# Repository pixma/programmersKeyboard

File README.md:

programmersKeyboard
===================
- Final Sem project

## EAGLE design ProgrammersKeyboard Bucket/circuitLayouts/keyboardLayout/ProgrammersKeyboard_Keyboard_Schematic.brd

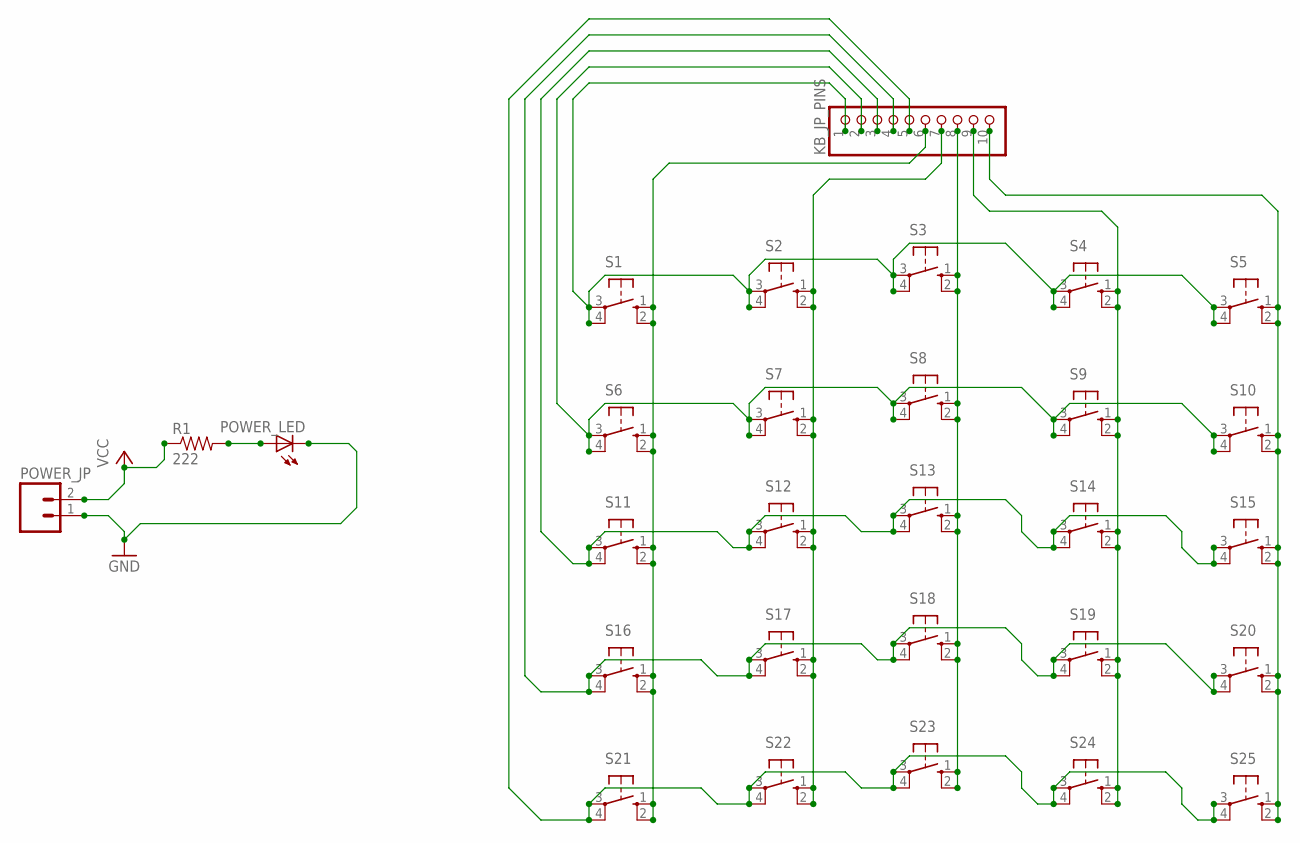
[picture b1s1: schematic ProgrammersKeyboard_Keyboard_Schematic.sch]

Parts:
KB_JP_PINS: PINHD-1X10/90; 1X10/90
POWER_JP: M02PTH3; 1X02_LONGPADS
POWER_LED: LEDSMT1206; 1206
R1: 222; 1206
S1, S2, S3, S4, S5, S6, S7, S8, S9, S10, S11, S12, S13, S14, S15, S16, S17, S18, S19, S20, S21, S22, S23, S24, S25: 10-XX; B3F-10XX

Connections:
GND: POWER_JP.1, POWER_LED.C
unnamed: KB_JP_PINS.3, S11.3, S11.4 (P1), S12.3, S12.4 (P1), S13.3, S13.4 (P1), S14.3, S14.4 (P1), S15.3, S15.4 (P1)
unnamed: KB_JP_PINS.4, S16.3, S16.4 (P1), S17.3, S17.4 (P1), S18.3, S18.4 (P1), S19.3, S19.4 (P1), S20.3, S20.4 (P1)
unnamed: KB_JP_PINS.5, S21.3, S21.4 (P1), S22.3, S22.4 (P1), S23.3, S23.4 (P1), S24.3, S24.4 (P1), S25.3, S25.4 (P1)
unnamed: POWER_LED.A, R1.2
unnamed: KB_JP_PINS.10, S5.1 (S), S5.2 (S1), S10.1 (S), S10.2 (S1), S15.1 (S), S15.2 (S1), S20.1 (S), S20.2 (S1), S25.1 (S), S25.2 (S1)
unnamed: KB_JP_PINS.6, S1.1 (S), S1.2 (S1), S6.1 (S), S6.2 (S1), S11.1 (S), S11.2 (S1), S16.1 (S), S16.2 (S1), S21.1 (S), S21.2 (S1)
unnamed: KB_JP_PINS.1, S1.3, S1.4 (P1), S2.3, S2.4 (P1), S3.3, S3.4 (P1), S4.3, S4.4 (P1), S5.3, S5.4 (P1)
unnamed: KB_JP_PINS.7, S2.1 (S), S2.2 (S1), S7.1 (S), S7.2 (S1), S12.1 (S), S12.2 (S1), S17.1 (S), S17.2 (S1), S22.1 (S), S22.2 (S1)
unnamed: KB_JP_PINS.8, S3.1 (S), S3.2 (S1), S8.1 (S), S8.2 (S1), S13.1 (S), S13.2 (S1), S18.1 (S), S18.2 (S1), S23.1 (S), S23.2 (S1)
unnamed: KB_JP_PINS.9, S4.1 (S), S4.2 (S1), S9.1 (S), S9.2 (S1), S14.1 (S), S14.2 (S1), S19.1 (S), S19.2 (S1), S24.1 (S), S24.2 (S1)
unnamed: KB_JP_PINS.2, S6.3, S6.4 (P1), S7.3, S7.4 (P1), S8.3, S8.4 (P1), S9.3, S9.4 (P1), S10.3, S10.4 (P1)
VCC: POWER_JP.2, R1.1

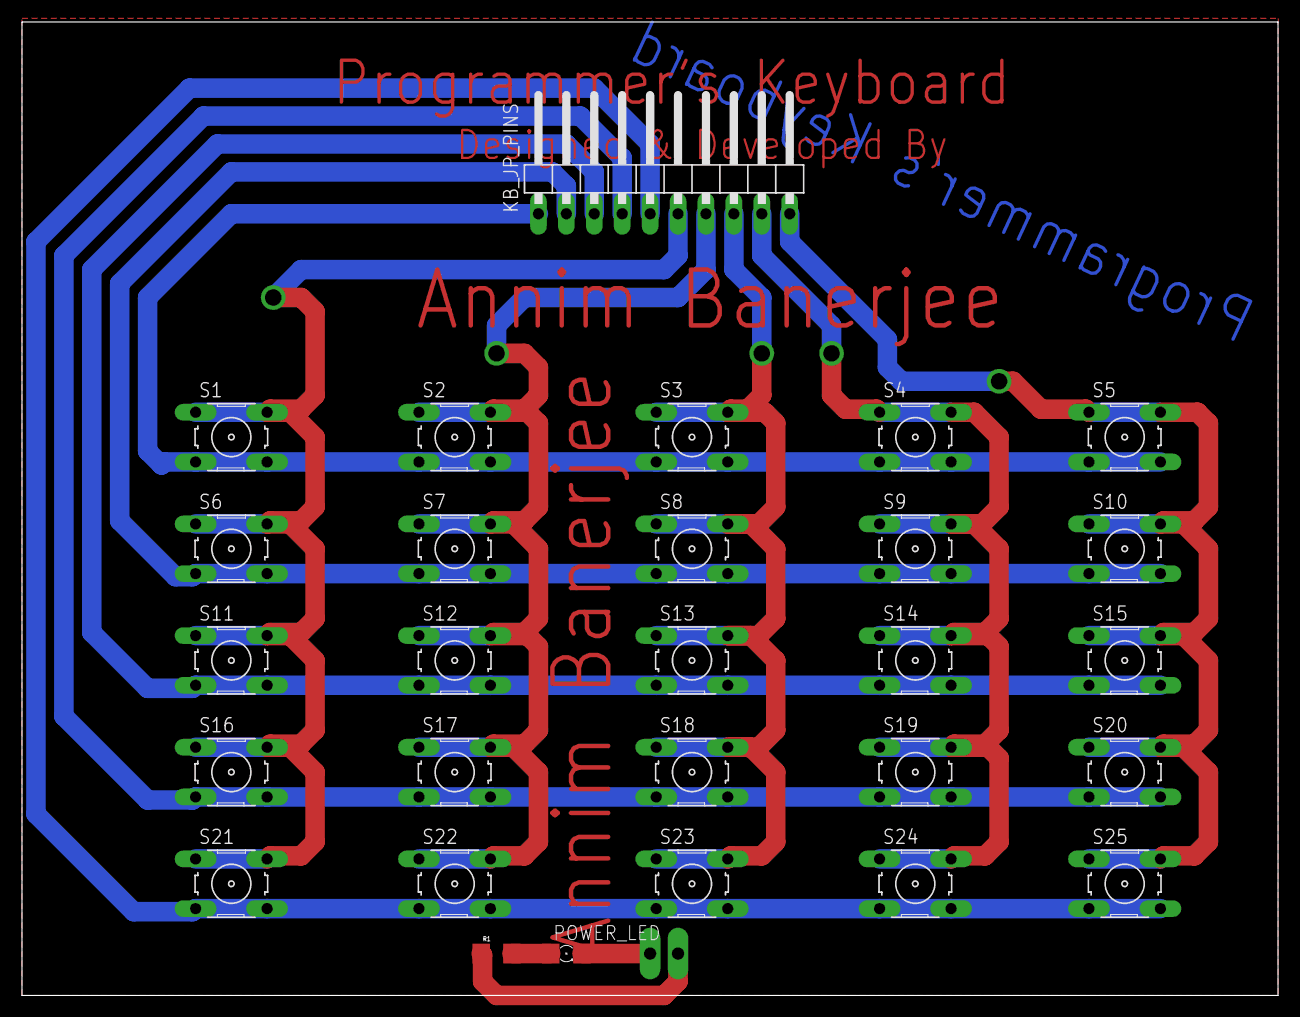
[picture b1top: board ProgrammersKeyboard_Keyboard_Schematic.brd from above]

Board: 2 copper layers, 114.3 x 88.6 mm, 29 parts (0 on the bottom side), 13 nets.

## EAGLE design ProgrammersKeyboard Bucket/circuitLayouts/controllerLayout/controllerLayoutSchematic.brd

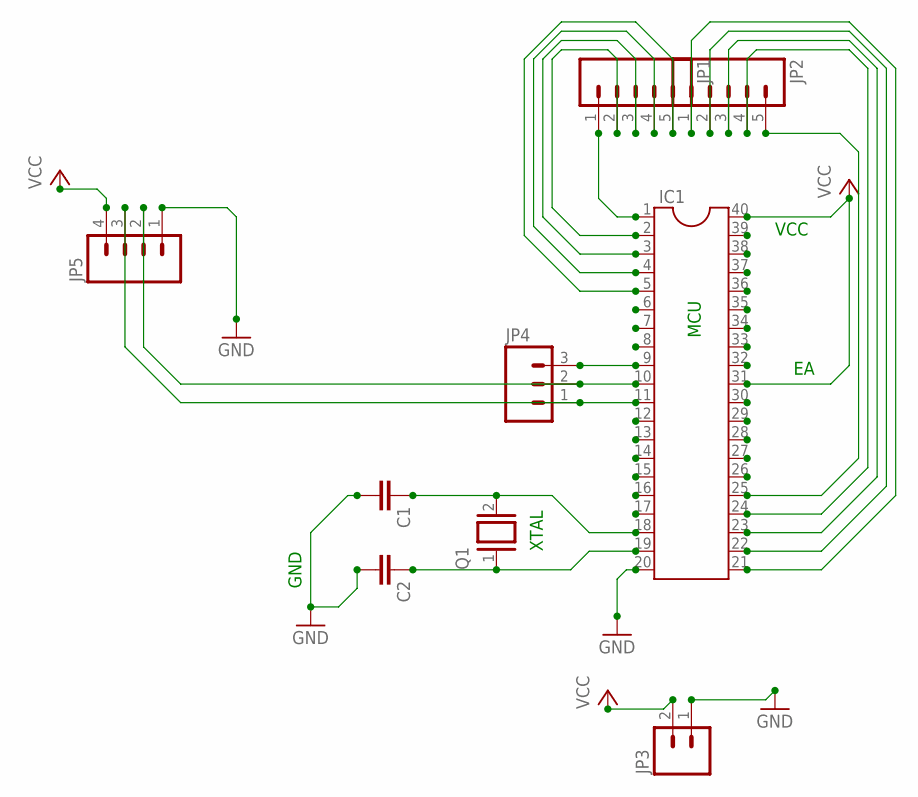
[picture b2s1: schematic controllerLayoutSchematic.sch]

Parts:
C1, C2: CAPPTH2; CAP-PTH-SMALL2
IC1: DIL40
JP1, JP2: M05PTH_LONGPADS; 1X05_LONGPADS
JP3: M02PTH3; 1X02_LONGPADS
JP4: M03LONGPADS; 1X03_LONGPADS
JP5: M04SMD; 1X04-SMD
Q1: XTAL; Q

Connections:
GND: C1.2, C2.2, IC1.20, JP3.1, JP5.1
unnamed: IC1.1, JP1.1
unnamed: IC1.9, JP4.3
unnamed: IC1.10, JP4.2, JP5.2
unnamed: IC1.11, JP4.1, JP5.3
unnamed: C1.1, IC1.18, Q1.2
unnamed: IC1.21, JP2.1
unnamed: IC1.23, JP2.3
unnamed: IC1.25, JP2.5
unnamed: IC1.24, JP2.4
unnamed: IC1.22, JP2.2
unnamed: IC1.5, JP1.5
unnamed: IC1.4, JP1.4
unnamed: IC1.3, JP1.3
unnamed: IC1.2, JP1.2
unnamed: C2.1, IC1.19, Q1.1
VCC: IC1.31, IC1.40, JP3.2, JP5.4

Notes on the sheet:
VCC
GND
XTAL
MCU

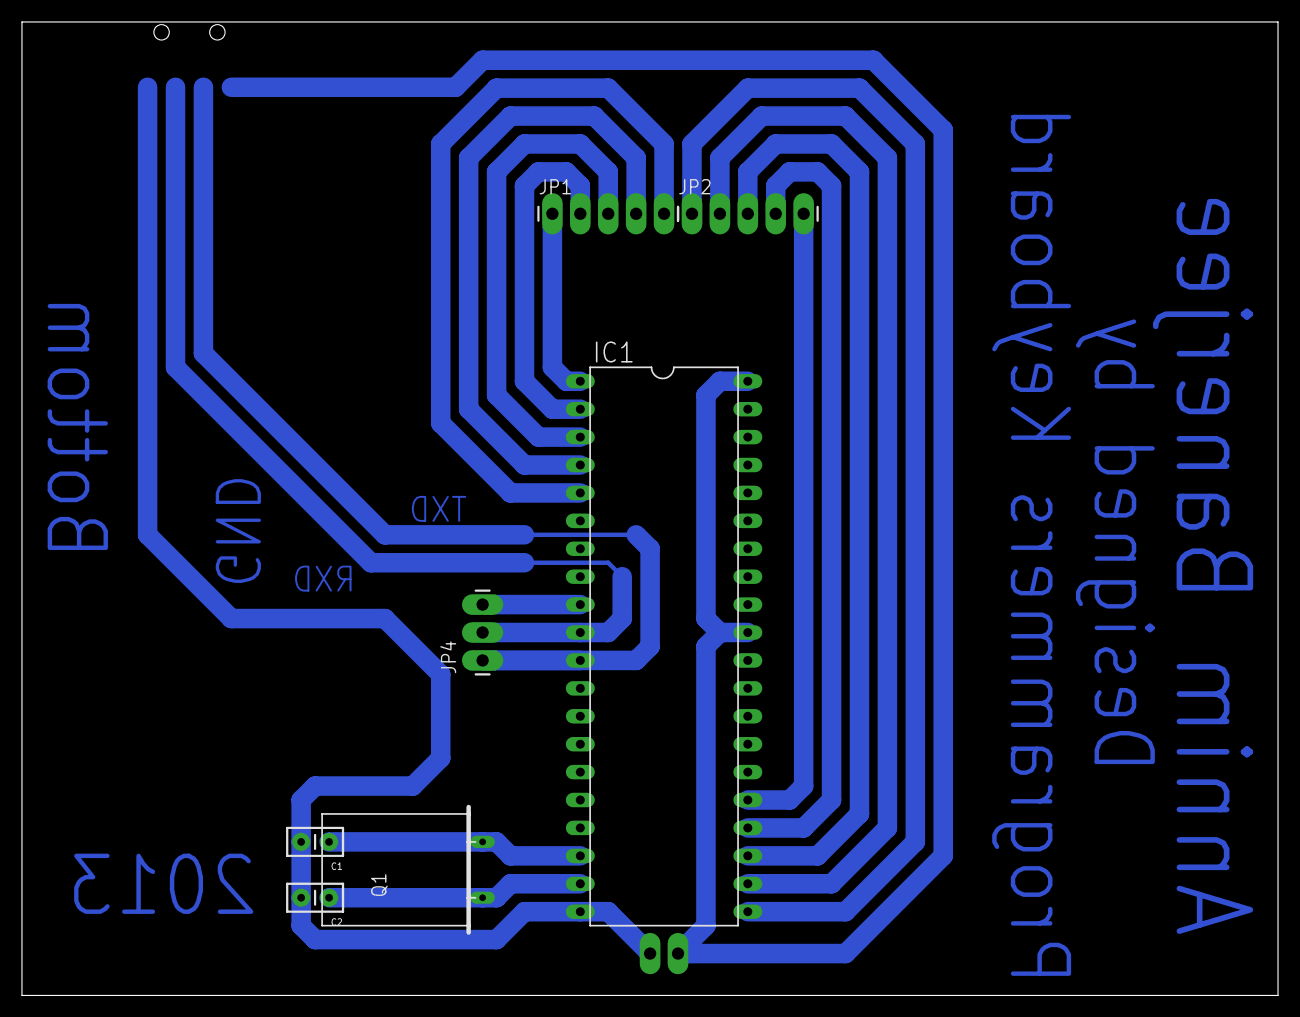
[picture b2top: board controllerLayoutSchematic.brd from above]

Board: 2 copper layers, 114.3 x 88.6 mm, 9 parts (1 on the bottom side), 17 nets.

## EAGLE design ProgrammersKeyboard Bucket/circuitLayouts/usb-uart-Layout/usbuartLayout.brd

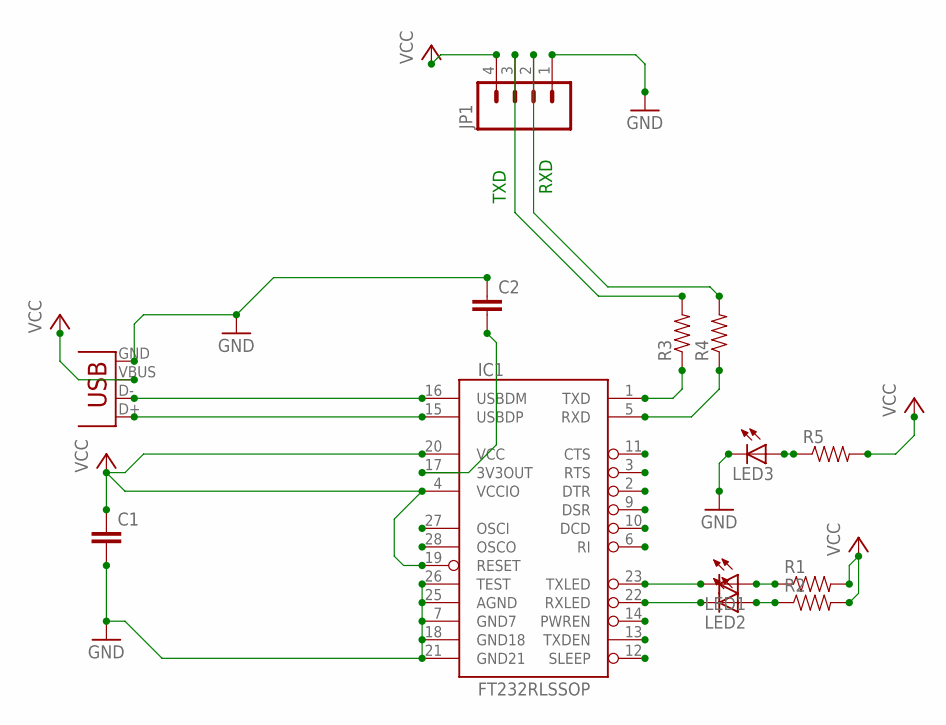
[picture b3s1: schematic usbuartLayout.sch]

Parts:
C1, C2: CAP1206; 1206
IC1: FT232RLSSOP; SSOP28DB
JP1: M04SMD; 1X04-SMD
LED1, LED2, LED3: LEDCHIPLED_1206; CHIPLED_1206
R1, R2, R3, R4, R5: RESISTOR1206; 1206
X1: USB-SMD-NS; USB-MINIB-NOSTOP

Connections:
GND: C1.2, C2.1, IC1.7 (GND7), IC1.18 (GND18), IC1.21 (GND21), IC1.25 (AGND), IC1.26 (TEST), JP1.1, LED3.C, X1.GND
unnamed: IC1.1 (TXD), R3.1
unnamed: JP1.3, R3.2
unnamed: IC1.15 (USBDP), X1.D+
unnamed: IC1.16 (USBDM), X1.D-
unnamed: LED3.A, R5.1
unnamed: C2.2, IC1.17 (3V3OUT)
unnamed: IC1.5 (RXD), R4.1
unnamed: JP1.2, R4.2
unnamed: IC1.22 (RXLED), LED2.C
unnamed: IC1.23 (TXLED), LED1.C
unnamed: LED2.A, R2.1
unnamed: LED1.A, R1.1
VCC: C1.1, IC1.4 (VCCIO), IC1.19 (RESET), IC1.20 (VCC), JP1.4, R1.2, R2.2, R5.2, X1.VBUS

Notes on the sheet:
TXD
RXD

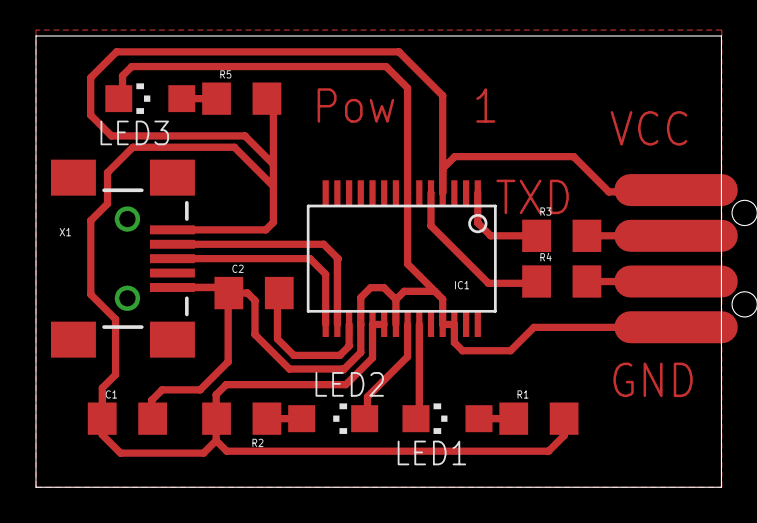
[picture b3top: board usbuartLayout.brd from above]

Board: 2 copper layers, 38.1 x 25.1 mm, 13 parts (0 on the bottom side), 14 nets.

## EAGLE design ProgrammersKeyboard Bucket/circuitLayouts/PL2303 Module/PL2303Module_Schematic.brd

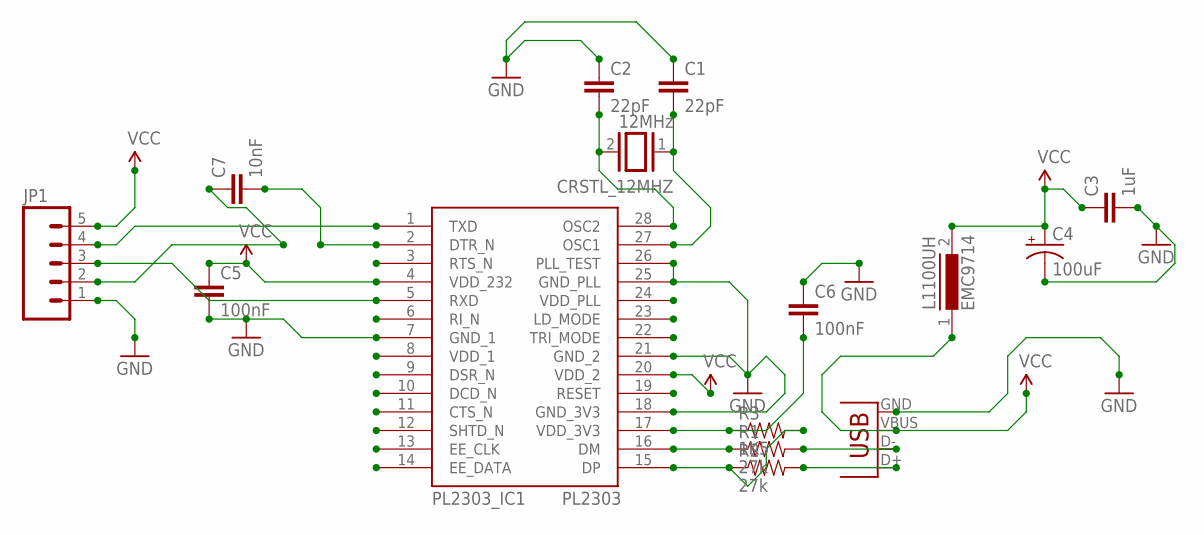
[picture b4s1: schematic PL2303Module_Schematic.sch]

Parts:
C1, C2: 22pF; 1206
C3: 1uF; CAP-PTH-SMALL2
C4: 100uF; CPOL-RADIAL-100UF-25V
C5: 100nF; CAP-PTH-SMALL2
C6: 100nF; 1206
C7: 10nF; 1206
CRSTL_12MHZ: 12MHz; Q
JP1: M05PTH_LONGPADS; 1X05_LONGPADS
L1100UH: EMC9714
PL2303_IC1: PL2303-SSOP28
R1, R2: 27k; 0805
R3: 1K5; 1206
X1: USBSMD; USB-MINIB

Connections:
GND: C1.1, C2.1, C3.2, C4.2 (-), C5.2, C6.1, JP1.1, PL2303_IC1.7 (GND_1), PL2303_IC1.18 (GND_3V3), PL2303_IC1.21 (GND_2), PL2303_IC1.25 (GND_PLL), PL2303_IC1.26 (PLL_TEST), X1.GND
unnamed: C7.1, JP1.2
unnamed: R1.2, X1.D-
unnamed: C7.2, PL2303_IC1.2 (DTR_N)
unnamed: C2.2, CRSTL_12MHZ.2, PL2303_IC1.28 (OSC2)
unnamed: C1.2, CRSTL_12MHZ.1, PL2303_IC1.27 (OSC1)
unnamed: PL2303_IC1.16 (DM), R1.1
unnamed: R2.2, X1.D+
unnamed: C6.2, PL2303_IC1.17 (VDD_3V3), R3.1
unnamed: JP1.3, PL2303_IC1.5 (RXD)
unnamed: PL2303_IC1.15 (DP), R2.1, R3.2
unnamed: JP1.4, PL2303_IC1.1 (TXD)
VCC: C3.1, C4.1 (+), C5.1, JP1.5, L1100UH.1, L1100UH.2, PL2303_IC1.4 (VDD_232), PL2303_IC1.20 (VDD_2), X1.VBUS

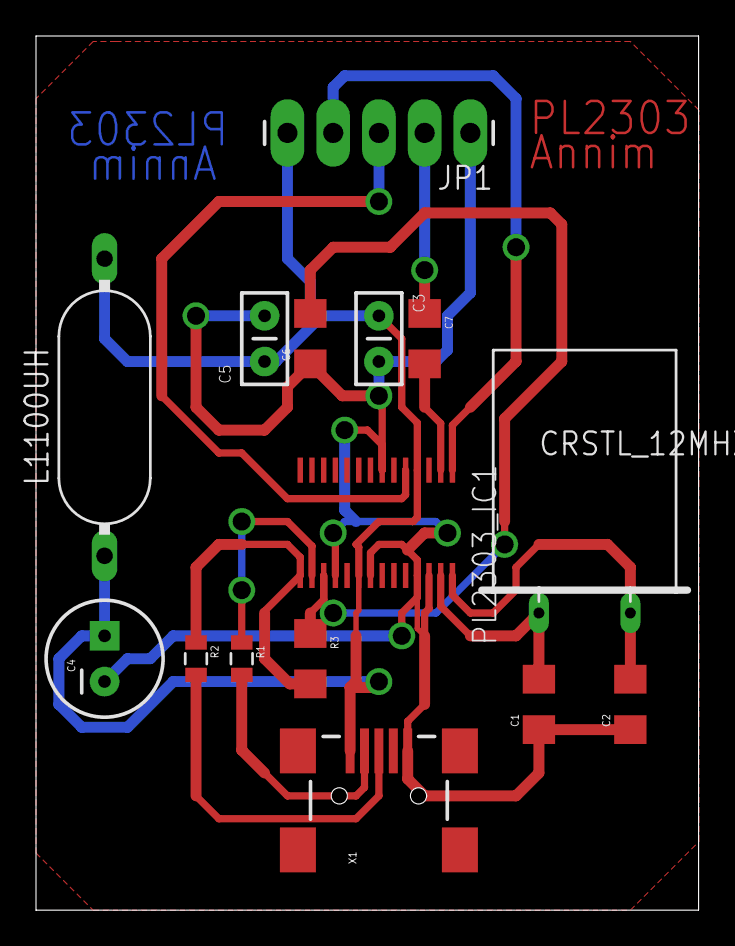
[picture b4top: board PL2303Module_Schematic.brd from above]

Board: 2 copper layers, 36.8 x 48.6 mm, 15 parts (0 on the bottom side), 13 nets.

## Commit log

2014-07-26 Content updated
2014-07-26 Inital Commit

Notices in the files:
parts and their libraries:
SparkFun-Connectors: Licensing: CC v3.0 Share-Alike You are welcome to use this library for commercial purposes.
